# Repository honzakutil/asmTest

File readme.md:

# asmTest
Kicad projekt pro test přepínání osazovacích variant pomocí pluginu kiAsm. Návrh není funkční (náhodné zapojení pinů procesoru, chybí mnoho součástek ...)

## osazovací varianty
- **def**: defaultní varianta. Pokud nejsou parametry součástky předefinovány v osazovací variantě, použije se to, co je v **def**
- **var1**: první osazovací varianta
- **var2**: druhá osazovací varianta

## test ručního přepínání variant - `kiAsm switch`
Před testem je projekt přepnutý do varianty **var1**, testovací posloupnost:
1) `git status`: zkontrolovat, že v repu nejsou necommitnuté změny - `kiAsm` mění soubory a opakované spuštění testu by mohlo dát jiný výsledek
2) přepnout na var2
3) vygenerovat podklady, porovnat se správnými daty (kontrola, jestli `kiAsm` přepíná přes **def** a nebo rovnou do **var2**)
4) přepnout na def
5) vygenerovat podkaldy, porovnat se správnými daty
6) přepnout na var1
7) vygenerovat podklady, porovnat se správnými daty
8) test začíná i končí **var1**, zkontrolovat pomocí `git status`, že není v souborech projektu rozdíl, případně vrátit testovací data do původního stavu - `git reset --hard HEAD`

## Jednotlivé součástky a co se jimi testuje
- R1 .. R6 - gate odpory výkonových tranzistorů, `Value` a `LCSC` jiné v každé variantě 
- Q1 .. Q6 - výkonové tranzistory, `Value` a `LCSC` jiné v každé variantě, se změnou varianty se mění i `Datasheet`
- R7, R8 - bočníky pro měření proudu, **var1** `Value` a **var1** `LCSC` nevyplněno, testuje se, že bude načteno z **def** i při přepnutí **var2** -> **var1**
- U1, U2, U3 - budiče driverů, obdobná situace jako R7, R8, ale **var1** `Value` a **var1** `LCSC` je změněné, kdežto **var2**  je shodné s **def**. Ve všech variantách je stejný `Datasheet` 
- FID1, FID2 - fiducial markery, nejsou v BOMu, ale jsou v PnP (aby si osazovači lehko zjistili souřadnice), s osazovací variantou se nemění
- LOGO1 - logo firmy jako součástka, nemá být v BOMu ani v PnP, se změnou osazovací varianty se nemění, řešeno pomocí `dnp`
- U4 - CAN driver - pro **var2** není osazený, testuje se funkce `dnp`. Pro **var2** se neobjeví v bomu ani v PnP, pro **def** a **var1** ano
- U5 - UART oddělovač - podobně jako U4, jenom prohozené **var1** a **var2**
- C10/C20 - kondenzátor pro test změny `Reference` - pro **var2** je přejmenovaný na C20, ve variantách **def** a **var1** je uvedený jako C10
- TODO: testování on_board a in_bom

## TODO: test správného zápisu změn z varianty do pracovních políček a zpátky
Před testem je projekt přepnutý do varianty **var1**, a má několik změn, které jsou jenom v pracovních políčkách kicadu a nejsou uložené do varianty. Pak následuje posloupnost:
1) gitem zkontrolovat, že v repu nejsou necommitnuté změny - `kiAsm` mění soubory a opakované spuštění testu by mohlo dát jiný výsledek
2) přepnout na var2
3) vygenerovat podklady, porovnat se správnými daty (kontrola, jestli `kiAsm` přepíná přes **def** a nebo rovnou do **var2**)
4) přepnout na def
5) vygenerovat podkaldy, porovnat se správnými daty (kontrola, co udělá prázdné a neexistující políčko u některých součástek pro varaintu **def**)
6) přepnout na var1
7) vygenerovat podklady, porovnat se správnými daty (kontrola, jestli se při přepnutí z **var1** uložila změněná data do varianty)
8) vrátit testovací data do původního stavu - `git reset --hard HEAD`

## TODO: součástky pro test práce s daty a udržování jejich konzistence
- C? C? C? - několik součástek přidaných bez zapnuté automatické anotace - TODO: jak by na to měl kiAsm reagovat?
- D1 - indikační dioda, pro **var1** je červená, jinak zelená - kromě změny `value` z red na green se testuje i změna custom políčka s (vymyšleným) LCSC katalogovým číslem. Red má katalogové číslo C12345, green má C67890
- R9 - druhý předřadný odpor pro diodu, pokud je dioda červená (**var1**), neosazuje se - vynechání z podkladů je řešeno přes JLCPCB_IGNORE, účelem je vyzkoušet, že kiAsm políčko JLCPCB_IGNORE z osatatních variant smaže, protože KiKit se rozhoduje podle existence tohoto políčka a ne podle jeho obsahu (prázdné políčko pořád existuje). Odpor se tedy musí objevit v datech **def** a **var2**, ale nesmí být ve **var1**
- U7 - LIN driver - ve **var2** se neosazuje, součástka přidaná do schématu později. Kromě políčka `var2 dnp` a `def Value` nemá žádná další políčka vytvořena - testuje se, jestli se kiAsm zachová správně k neexistujícím políčkům - tedy že si načte Value z **def** 

TODO: naroutovat a upravit sch i pcb tak, aby prošlo DRC a bylo možné generovat pohodlně bom, gerber data atd ...

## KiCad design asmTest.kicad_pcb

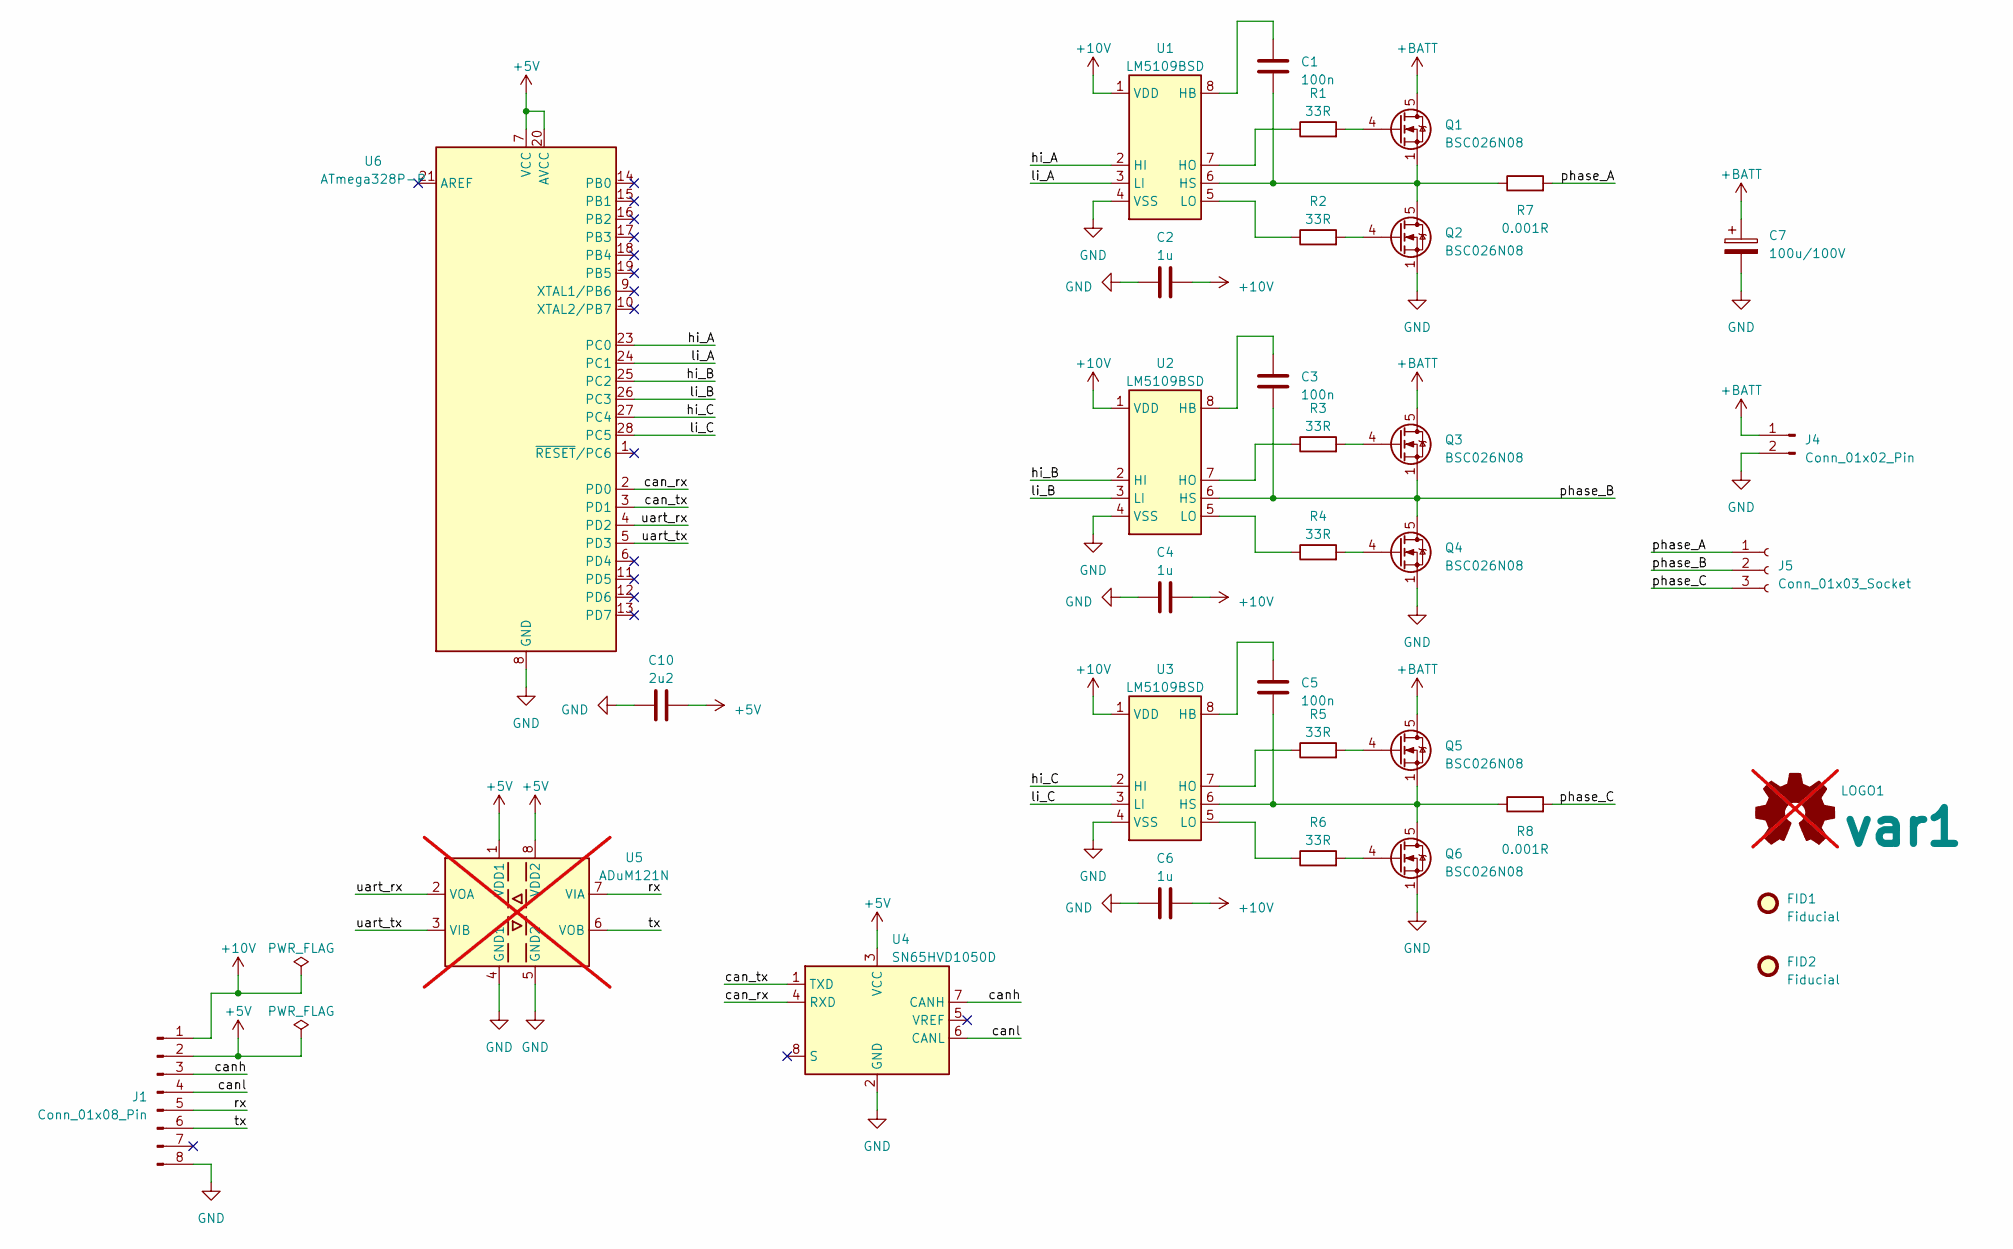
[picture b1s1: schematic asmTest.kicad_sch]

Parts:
C1, C3, C5: 100n; C_0603_1608Metric; LCSC C01
C2, C4, C6: 1u; C_1206_3216Metric; LCSC C02
C7: 100u/100V; CP_Radial_D10.0mm_P5.00mm; LCSC C03
C10: 2u2; C_1206_3216Metric; LCSC C04
FID1, FID2: Fiducial; Fiducial_1mm_Mask3mm
J1: Conn_01x08_Pin; PinSocket_1x08_P2.54mm_Vertical; LCSC C06
J4: Conn_01x02_Pin; PinHeader_1x02_P2.54mm_Vertical; LCSC C07
J5: Conn_01x03_Socket; PinSocket_1x03_P2.54mm_Horizontal; LCSC C08
LOGO1: var1; OSHW-Logo2_9.8x8mm_Copper; not fitted
Q1, Q2, Q3, Q4, Q5, Q6: BSC026N08; TDSON-8-1; LCSC C50
R1, R2, R3, R4, R5, R6: 33R; R_0603_1608Metric; LCSC C51
R7, R8: 0.001R; R_2512_6332Metric; LCSC C12
U1, U2, U3: LM5109BSD; WSON-8-1EP_4x4mm_P0.8mm_EP2.6x3mm; LCSC C52
U4: SN65HVD1050D; SOIC-8_3.9x4.9mm_P1.27mm; LCSC C14
U5: ADuM121N; SOIC-8_3.9x4.9mm_P1.27mm; LCSC C15; not fitted
U6: ATmega328P-P; DIP-28_W7.62mm; LCSC C16

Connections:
+5V: C10.1, J1.2, U4.3 (VCC), U5.1 (VDD1), U5.8 (VDD2), U6.7 (VCC), U6.20 (AVCC)
+10V: C2.1, C4.1, C6.1, J1.1, U1.1 (VDD), U2.1 (VDD), U3.1 (VDD)
+BATT: C7.1, J4.1, Q1.5 (D), Q3.5 (D), Q5.5 (D)
/can_rx: U4.4 (RXD), U6.2 (PD0)
/can_tx: U4.1 (TXD), U6.3 (PD1)
/canh: J1.3, U4.7 (CANH)
/canl: J1.4, U4.6 (CANL)
/hi_A: U1.2 (HI), U6.23 (PC0)
/hi_B: U2.2 (HI), U6.25 (PC2)
/hi_C: U3.2 (HI), U6.27 (PC4)
/li_A: U1.3 (LI), U6.24 (PC1)
/li_B: U2.3 (LI), U6.26 (PC3)
/li_C: U3.3 (LI), U6.28 (PC5)
/phase_A: J5.1, R7.2
/phase_B: C3.2, J5.2, Q3.1 (S), Q3.2 (S), Q3.3 (S), Q4.5 (D), U2.6 (HS)
/phase_C: J5.3, R8.2
/rx: J1.5, U5.7 (VIA)
/tx: J1.6, U5.6 (VOB)
/uart_rx: U5.2 (VOA), U6.4 (PD2)
/uart_tx: U5.3 (VIB), U6.5 (PD3)
GND: C2.2, C4.2, C6.2, C7.2, C10.2, J1.8, J4.2, Q2.1 (S), Q2.2 (S), Q2.3 (S), Q4.1 (S), Q4.2 (S), Q4.3 (S), Q6.1 (S), Q6.2 (S), Q6.3 (S), U1.4 (VSS), U1.9 (VSS), U2.4 (VSS), U2.9 (VSS), U3.4 (VSS), U3.9 (VSS), U4.2 (GND), U5.4 (GND1), U5.5 (GND2), U6.8 (GND), U6.22 (GND)
unnamed: Q1.4 (G), R1.2
unnamed: C1.2, Q1.1 (S), Q1.2 (S), Q1.3 (S), Q2.5 (D), R7.1, U1.6 (HS)
unnamed: Q2.4 (G), R2.2
unnamed: Q3.4 (G), R3.2
unnamed: Q4.4 (G), R4.2
unnamed: Q5.4 (G), R5.2
unnamed: C5.2, Q5.1 (S), Q5.2 (S), Q5.3 (S), Q6.5 (D), R8.1, U3.6 (HS)
unnamed: Q6.4 (G), R6.2
unnamed: C1.1, U1.8 (HB)
unnamed: R1.1, U1.7 (HO)
unnamed: R2.1, U1.5 (LO)
unnamed: C3.1, U2.8 (HB)
unnamed: R3.1, U2.7 (HO)
unnamed: R4.1, U2.5 (LO)
unnamed: C5.1, U3.8 (HB)
unnamed: R5.1, U3.7 (HO)
unnamed: R6.1, U3.5 (LO)

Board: 2 copper layers, 34 parts (0 on the bottom side), 38 nets, no tracks yet.

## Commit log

2023-03-09 first iteration of test
2023-03-09 add test script and correct output files
2023-03-09 add fictional LCSC PN to test switching of user-defined fields
